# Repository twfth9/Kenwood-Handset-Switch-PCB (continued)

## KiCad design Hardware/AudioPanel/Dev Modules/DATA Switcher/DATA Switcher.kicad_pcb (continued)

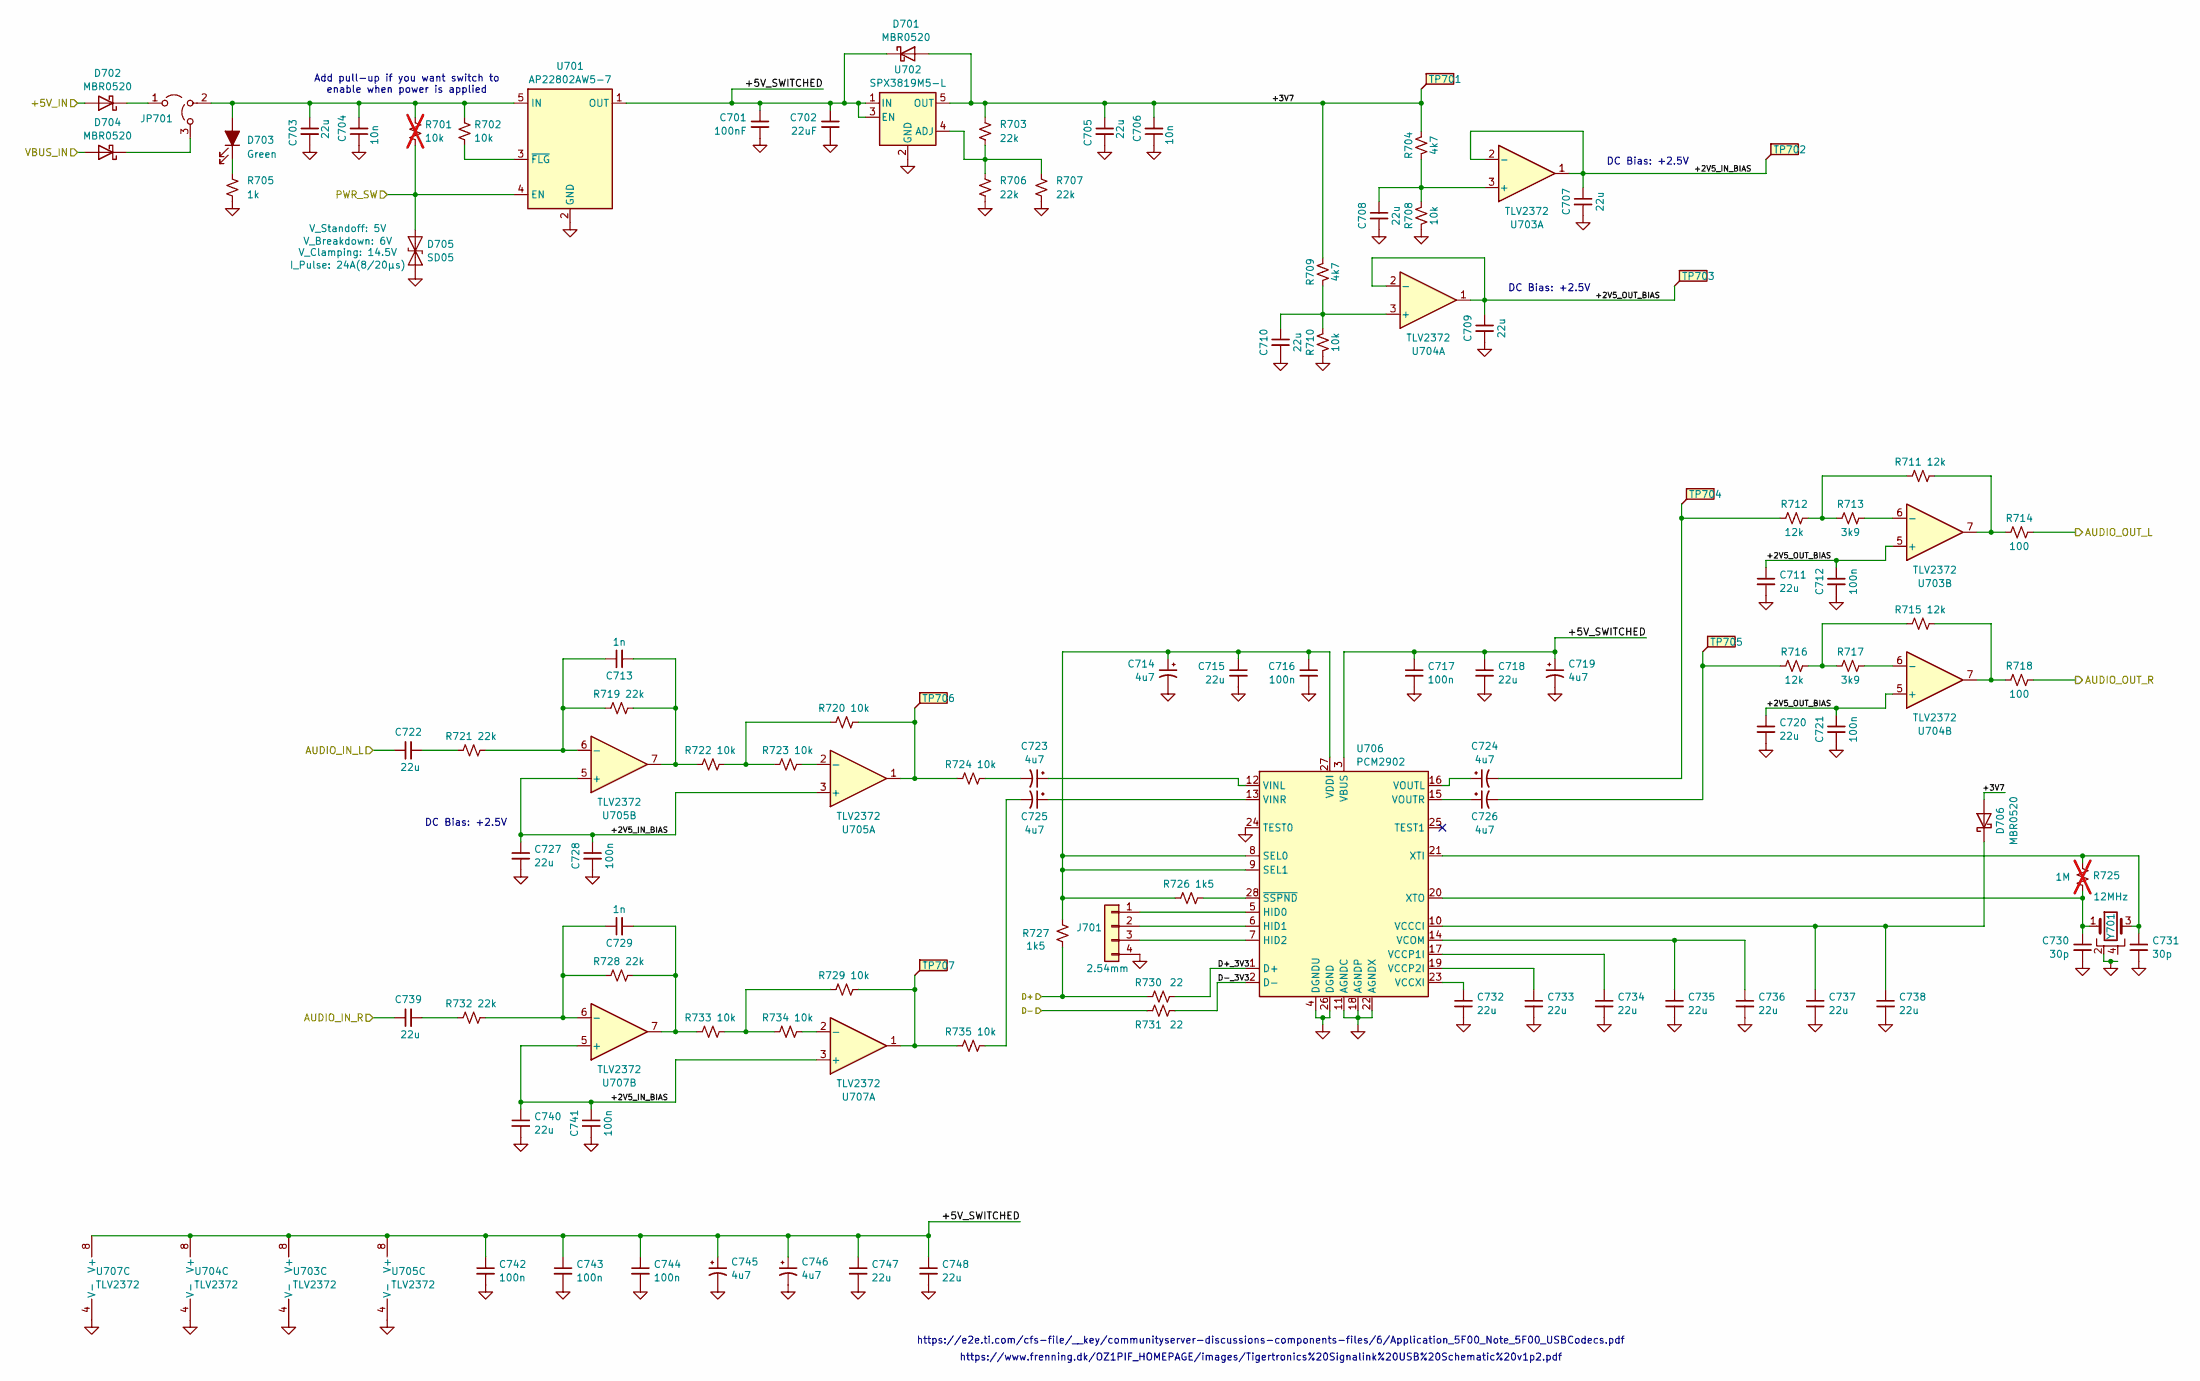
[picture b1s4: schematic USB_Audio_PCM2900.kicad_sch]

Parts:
C701: 100nF; Worthington_C_0402
C702: 22uF; Worthington_C_0603
C703, C705, C707, C708, C709, C710, C711, C715, C718, C720, C722, C727, C732, C733, C734, C735, C736, C737, C738, C739, C740, C747, C748: 22u; Worthington_C_0603
C704, C706: 10n; Worthington_C_0402
C712, C716, C717, C721, C728, C741, C742, C743, C744: 100n; Worthington_C_0402
C713, C729: 1n; Worthington_C_0402
C714, C719, C723, C724, C725, C726, C745, C746: 4u7; CP_EIA-3216-18_Kemet-A
C730, C731: 30p; Worthington_C_0402
D701, D702, D704, D706: MBR0520; D_SOD-123
D703: Green; Worthington_LED_0603; DigiKey Part Number 732-5016-ND
D705: SD05; D_SOD-323
J701: 2.54mm; PinHeader_1x04_P2.54mm_Vertical
JP701: Jumper_3_Open; SolderBridge_3L
R701: 10k; Worthington_R_0402; not fitted
R702, R708, R710, R720, R722, R723, R724, R729, R733, R734, R735: 10k; Worthington_R_0402
R703, R706, R707: 22k; Worthington_R_0402; DigiKey Part Number 311-510HRCT-ND
R704, R709: 4k7; Worthington_R_0402
R705: 1k; Worthington_R_0402; DigiKey Part Number 311-510HRCT-ND
R711, R712, R715, R716: 12k; Worthington_R_0402
R713, R717: 3k9; Worthington_R_0402
R714, R718: 100; Worthington_R_0402
R719, R721, R728, R732: 22k; Worthington_R_0402
R725: 1M; Worthington_R_0402; not fitted
R726, R727: 1k5; Worthington_R_0402
R730, R731: 22; Worthington_R_0402
TP701, TP702, TP703, TP704, TP705, TP706, TP707: TestPoint_Flag; KEYSTONE_5017
U701: AP22802AW5-7; SC-74A-5_1.55x2.9mm_P0.95mm
U702: SPX3819M5-L; SOT-23-5
U703, U704, U705, U707: TLV2372; SOIC-8_3.9x4.9mm_P1.27mm
U706: PCM2902; SSOP-28_5.3x10.2mm_P0.65mm
Y701: 12MHz; Crystal_SMD_Abracon_ABM8AIG-4Pin_3.2x2.5mm

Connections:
/+5V_RIGCTRL1: D702.2 (A); also elsewhere on the board
/RIGCTRL_1.D+: R727.2, R730.2; also elsewhere on the board
/RIGCTRL_1.D-: R731.1; also elsewhere on the board
/RIGCTRL_1.PWR_SW: D705.2 (A2), R701.2, U701.4 (EN); also elsewhere on the board
/RIGCTRL_1.RX1: C722.1; also elsewhere on the board
/RIGCTRL_1.RX2: C739.1; also elsewhere on the board
/RIGCTRL_1.TX1: R714.1; also elsewhere on the board
/RIGCTRL_1.TX2: R718.1; also elsewhere on the board
/RIGCTRL_1.VBUS: D704.2 (A); also elsewhere on the board
/USB Audio Interface - RIGCTRL1/+2V5_IN_BIAS: C707.1, C727.1, C728.1, C740.1, C741.1, TP702.1, U703.1, U703.2 (-), U705.3 (+), U705.5 (+), U707.3 (+), U707.5 (+)
/USB Audio Interface - RIGCTRL1/+2V5_OUT_BIAS: C709.1, C711.1, C712.1, C720.1, C721.1, TP703.1, U703.5 (+), U704.1, U704.2 (-), U704.5 (+)
/USB Audio Interface - RIGCTRL1/+3V7: C705.1, C706.2, D701.2 (A), D706.2 (A), R703.2, R704.2, R709.2, TP701.1, U702.5 (OUT)
/USB Audio Interface - RIGCTRL1/+5V_SWITCHED: C701.1, C702.1, C717.1, C718.1, C719.1, C742.1, C743.1, C744.1, C745.1, C746.1, C747.1, C748.1, D701.1 (K), U701.1 (OUT), U702.1 (IN), U702.3 (EN), U703.8 (V+), U704.8 (V+), U705.8 (V+), U706.3 (VBUS), U707.8 (V+)
/USB Audio Interface - RIGCTRL1/D+_3V3: R730.1, U706.1 (D+)
/USB Audio Interface - RIGCTRL1/D-_3V3: R731.2, U706.2 (D-)
GND: C701.2, C702.2, C703.2, C704.1, C705.2, C706.1, C707.2, C708.2, C709.2, C710.2, C711.2, C712.2, C714.2, C715.2, C716.2, C717.2, C718.2, C719.2, C720.2, C721.2, C727.2, C728.2, C730.2, C731.2, C732.2, C733.2, C734.2, C735.2, C736.2, C737.2, C738.2, C740.2, C741.2, C742.2, C743.2, C744.2, C745.2, C746.2, C747.2, C748.2, D705.1 (A1), J701.4, R705.1, R706.1, R707.1, R708.1, R710.1, U701.2 (GND), U702.2 (GND), U703.4 (V-), U704.4 (V-), U705.4 (V-), U706.4 (DGNDU), U706.11 (AGNDC), U706.18 (AGNDP), U706.22 (AGNDX), U706.24 (TEST0), U706.26 (DGND), U707.4 (V-), Y701.2; also elsewhere on the board
unnamed: C713.2, R719.1, R722.2, U705.7
unnamed: C722.2, R721.2
unnamed: C723.2, R724.1
unnamed: C724.2, R712.2, TP704.1
unnamed: C725.2, R735.1
unnamed: C726.2, R716.2, TP705.1
unnamed: C729.2, R728.1, R733.2, U707.7
unnamed: C739.2, R732.2
unnamed: D702.1 (K), JP701.1 (A)
unnamed: C703.1, C704.2, D703.2 (A), JP701.2 (C), R701.1, R702.1, U701.5 (IN)
unnamed: D703.1 (K), R705.2
unnamed: D704.1 (K), JP701.3 (B)
unnamed: C737.1, C738.1, D706.1 (K), U706.10 (VCCCI)
unnamed: J701.1, U706.5 (HID0)
unnamed: J701.2, U706.6 (HID1)
unnamed: J701.3, U706.7 (HID2)
unnamed: R711.1, R714.2, U703.7
unnamed: R711.2, R712.1, R713.2
unnamed: R715.1, R718.2, U704.7
unnamed: R715.2, R716.1, R717.2
unnamed: R720.1, R724.2, TP706.1, U705.1
unnamed: R720.2, R722.1, R723.2
unnamed: R729.1, R735.2, TP707.1, U707.1
unnamed: R729.2, R733.1, R734.2
unnamed: R702.2, U701.3 (~FLG)
unnamed: R703.1, R706.2, R707.2, U702.4 (ADJ)
unnamed: C708.1, R704.1, R708.2, U703.3 (+)
unnamed: R713.1, U703.6 (-)
unnamed: C710.1, R709.1, R710.2, U704.3 (+)
unnamed: R717.1, U704.6 (-)
unnamed: R723.1, U705.2 (-)
unnamed: C713.1, R719.2, R721.1, U705.6 (-)
unnamed: C714.1, C715.1, C716.1, R726.2, R727.1, U706.8 (SEL0), U706.9 (SEL1), U706.27 (VDDI)
unnamed: C734.1, U706.17 (VCCP1I)
unnamed: C733.1, U706.19 (VCCP2I)
unnamed: C732.1, U706.23 (VCCXI)
unnamed: C735.1, C736.1, U706.14 (VCOM)
unnamed: C723.1, U706.12 (VINL)
unnamed: C725.1, U706.13 (VINR)
unnamed: C724.1, U706.16 (VOUTL)
unnamed: C726.1, U706.15 (VOUTR)
unnamed: C731.1, R725.1, U706.21 (XTI), Y701.3
unnamed: C730.1, R725.2, U706.20 (XTO), Y701.1
unnamed: R726.1, U706.28 (~SSPND)
unnamed: R734.1, U707.2 (-)
unnamed: C729.1, R728.2, R732.1, U707.6 (-)

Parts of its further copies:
C801: 100nF; Worthington_C_0402
C802: 22uF; Worthington_C_0603
C803, C805, C807, C808, C809, C810, C811, C815, C818, C820, C822, C827, C832, C833, C834, C835, C836, C837, C838, C839, C840, C847, C848: 22u; Worthington_C_0603
C804, C806: 10n; Worthington_C_0402
C812, C816, C817, C821, C828, C841, C842, C843, C844: 100n; Worthington_C_0402
C813, C829: 1n; Worthington_C_0402
C814, C819, C823, C824, C825, C826, C845, C846: 4u7; CP_EIA-3216-18_Kemet-A
C830, C831: 30p; Worthington_C_0402
D801, D802, D804, D806: MBR0520; D_SOD-123
D803: Green; Worthington_LED_0603; DigiKey Part Number 732-5016-ND
D805: SD05; D_SOD-323
J801: 2.54mm; PinHeader_1x04_P2.54mm_Vertical
JP801: Jumper_3_Open; SolderBridge_3L
R801: 10k; Worthington_R_0402; not fitted
R802, R808, R810, R820, R822, R823, R824, R829, R833, R834, R835: 10k; Worthington_R_0402
R803, R806, R807: 22k; Worthington_R_0402; DigiKey Part Number 311-510HRCT-ND
R804, R809: 4k7; Worthington_R_0402
R805: 1k; Worthington_R_0402; DigiKey Part Number 311-510HRCT-ND
R811, R812, R815, R816: 12k; Worthington_R_0402
R813, R817: 3k9; Worthington_R_0402
R814, R818: 100; Worthington_R_0402
R819, R821, R828, R832: 22k; Worthington_R_0402
R825: 1M; Worthington_R_0402; not fitted
R826, R827: 1k5; Worthington_R_0402
R830, R831: 22; Worthington_R_0402
TP801, TP802, TP803, TP804, TP805, TP806, TP807: TestPoint_Flag; KEYSTONE_5017
U801: AP22802AW5-7; SC-74A-5_1.55x2.9mm_P0.95mm
U802: SPX3819M5-L; SOT-23-5
U803, U804, U805, U807: TLV2372; SOIC-8_3.9x4.9mm_P1.27mm
U806: PCM2902; SSOP-28_5.3x10.2mm_P0.65mm
Y801: 12MHz; Crystal_SMD_Abracon_ABM8AIG-4Pin_3.2x2.5mm

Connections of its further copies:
/+5V_RIGCTRL2: D802.2 (A); also elsewhere on the board
/RIGCTRL_2.D+: R827.2, R830.2; also elsewhere on the board
/RIGCTRL_2.D-: R831.1; also elsewhere on the board
/RIGCTRL_2.PWR_SW: D805.2 (A2), R801.2, U801.4 (EN); also elsewhere on the board
/RIGCTRL_2.RX1: C822.1; also elsewhere on the board
/RIGCTRL_2.RX2: C839.1; also elsewhere on the board
/RIGCTRL_2.TX1: R814.1; also elsewhere on the board
/RIGCTRL_2.TX2: R818.1; also elsewhere on the board
/RIGCTRL_2.VBUS: D804.2 (A); also elsewhere on the board
/USB Audio Interface - RIGCTRL2/+2V5_IN_BIAS: C807.1, C827.1, C828.1, C840.1, C841.1, TP802.1, U803.1, U803.2 (-), U805.3 (+), U805.5 (+), U807.3 (+), U807.5 (+)
/USB Audio Interface - RIGCTRL2/+2V5_OUT_BIAS: C809.1, C811.1, C812.1, C820.1, C821.1, TP803.1, U803.5 (+), U804.1, U804.2 (-), U804.5 (+)
/USB Audio Interface - RIGCTRL2/+3V7: C805.1, C806.2, D801.2 (A), D806.2 (A), R803.2, R804.2, R809.2, TP801.1, U802.5 (OUT)
/USB Audio Interface - RIGCTRL2/+5V_SWITCHED: C801.1, C802.1, C817.1, C818.1, C819.1, C842.1, C843.1, C844.1, C845.1, C846.1, C847.1, C848.1, D801.1 (K), U801.1 (OUT), U802.1 (IN), U802.3 (EN), U803.8 (V+), U804.8 (V+), U805.8 (V+), U806.3 (VBUS), U807.8 (V+)
/USB Audio Interface - RIGCTRL2/D+_3V3: R830.1, U806.1 (D+)
/USB Audio Interface - RIGCTRL2/D-_3V3: R831.2, U806.2 (D-)
GND: C801.2, C802.2, C803.2, C804.1, C805.2, C806.1, C807.2, C808.2, C809.2, C810.2, C811.2, C812.2, C814.2, C815.2, C816.2, C817.2, C818.2, C819.2, C820.2, C821.2, C827.2, C828.2, C830.2, C831.2, C832.2, C833.2, C834.2, C835.2, C836.2, C837.2, C838.2, C840.2, C841.2, C842.2, C843.2, C844.2, C845.2, C846.2, C847.2, C848.2, D805.1 (A1), J801.4, R805.1, R806.1, R807.1, R808.1, R810.1, U801.2 (GND), U802.2 (GND), U803.4 (V-), U804.4 (V-), U805.4 (V-), U806.4 (DGNDU), U806.11 (AGNDC), U806.18 (AGNDP), U806.22 (AGNDX), U806.24 (TEST0), U806.26 (DGND), U807.4 (V-), Y801.2; also elsewhere on the board
unnamed: C813.2, R819.1, R822.2, U805.7
unnamed: C822.2, R821.2
unnamed: C823.2, R824.1
unnamed: C824.2, R812.2, TP804.1
unnamed: C825.2, R835.1
unnamed: C826.2, R816.2, TP805.1
unnamed: C829.2, R828.1, R833.2, U807.7
unnamed: C839.2, R832.2
unnamed: D802.1 (K), JP801.1 (A)
unnamed: C803.1, C804.2, D803.2 (A), JP801.2 (C), R801.1, R802.1, U801.5 (IN)
unnamed: D803.1 (K), R805.2
unnamed: D804.1 (K), JP801.3 (B)
unnamed: C837.1, C838.1, D806.1 (K), U806.10 (VCCCI)
unnamed: J801.1, U806.5 (HID0)
unnamed: J801.2, U806.6 (HID1)
unnamed: J801.3, U806.7 (HID2)
unnamed: R811.1, R814.2, U803.7
unnamed: R811.2, R812.1, R813.2
unnamed: R815.1, R818.2, U804.7
unnamed: R815.2, R816.1, R817.2
unnamed: R820.1, R824.2, TP806.1, U805.1
unnamed: R820.2, R822.1, R823.2
unnamed: R829.1, R835.2, TP807.1, U807.1
unnamed: R829.2, R833.1, R834.2
unnamed: R802.2, U801.3 (~FLG)
unnamed: R803.1, R806.2, R807.2, U802.4 (ADJ)
unnamed: C808.1, R804.1, R808.2, U803.3 (+)
unnamed: R813.1, U803.6 (-)
unnamed: C810.1, R809.1, R810.2, U804.3 (+)
unnamed: R817.1, U804.6 (-)
unnamed: R823.1, U805.2 (-)
unnamed: C813.1, R819.2, R821.1, U805.6 (-)
unnamed: C814.1, C815.1, C816.1, R826.2, R827.1, U806.8 (SEL0), U806.9 (SEL1), U806.27 (VDDI)
unnamed: C834.1, U806.17 (VCCP1I)
unnamed: C833.1, U806.19 (VCCP2I)
unnamed: C832.1, U806.23 (VCCXI)
unnamed: C835.1, C836.1, U806.14 (VCOM)
unnamed: C823.1, U806.12 (VINL)
unnamed: C825.1, U806.13 (VINR)
unnamed: C824.1, U806.16 (VOUTL)
unnamed: C826.1, U806.15 (VOUTR)
unnamed: C831.1, R825.1, U806.21 (XTI), Y801.3
unnamed: C830.1, R825.2, U806.20 (XTO), Y801.1
unnamed: R826.1, U806.28 (~SSPND)
unnamed: R834.1, U807.2 (-)
unnamed: C829.1, R828.2, R832.1, U807.6 (-)

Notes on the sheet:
DC Bias: +2.5V
Add pull-up if you want switch to enable when power is applied
https://www.frenning.dk/OZ1PIF_HOMEPAGE/images/Tigertronics%20Signalink%20USB%20Schematic%20v1p2.pdf
https://e2e.ti.com/cfs-file/__key/communityserver-discussions-components-files/6/Application_5F00_Note_5F00_USBCodecs.pdf

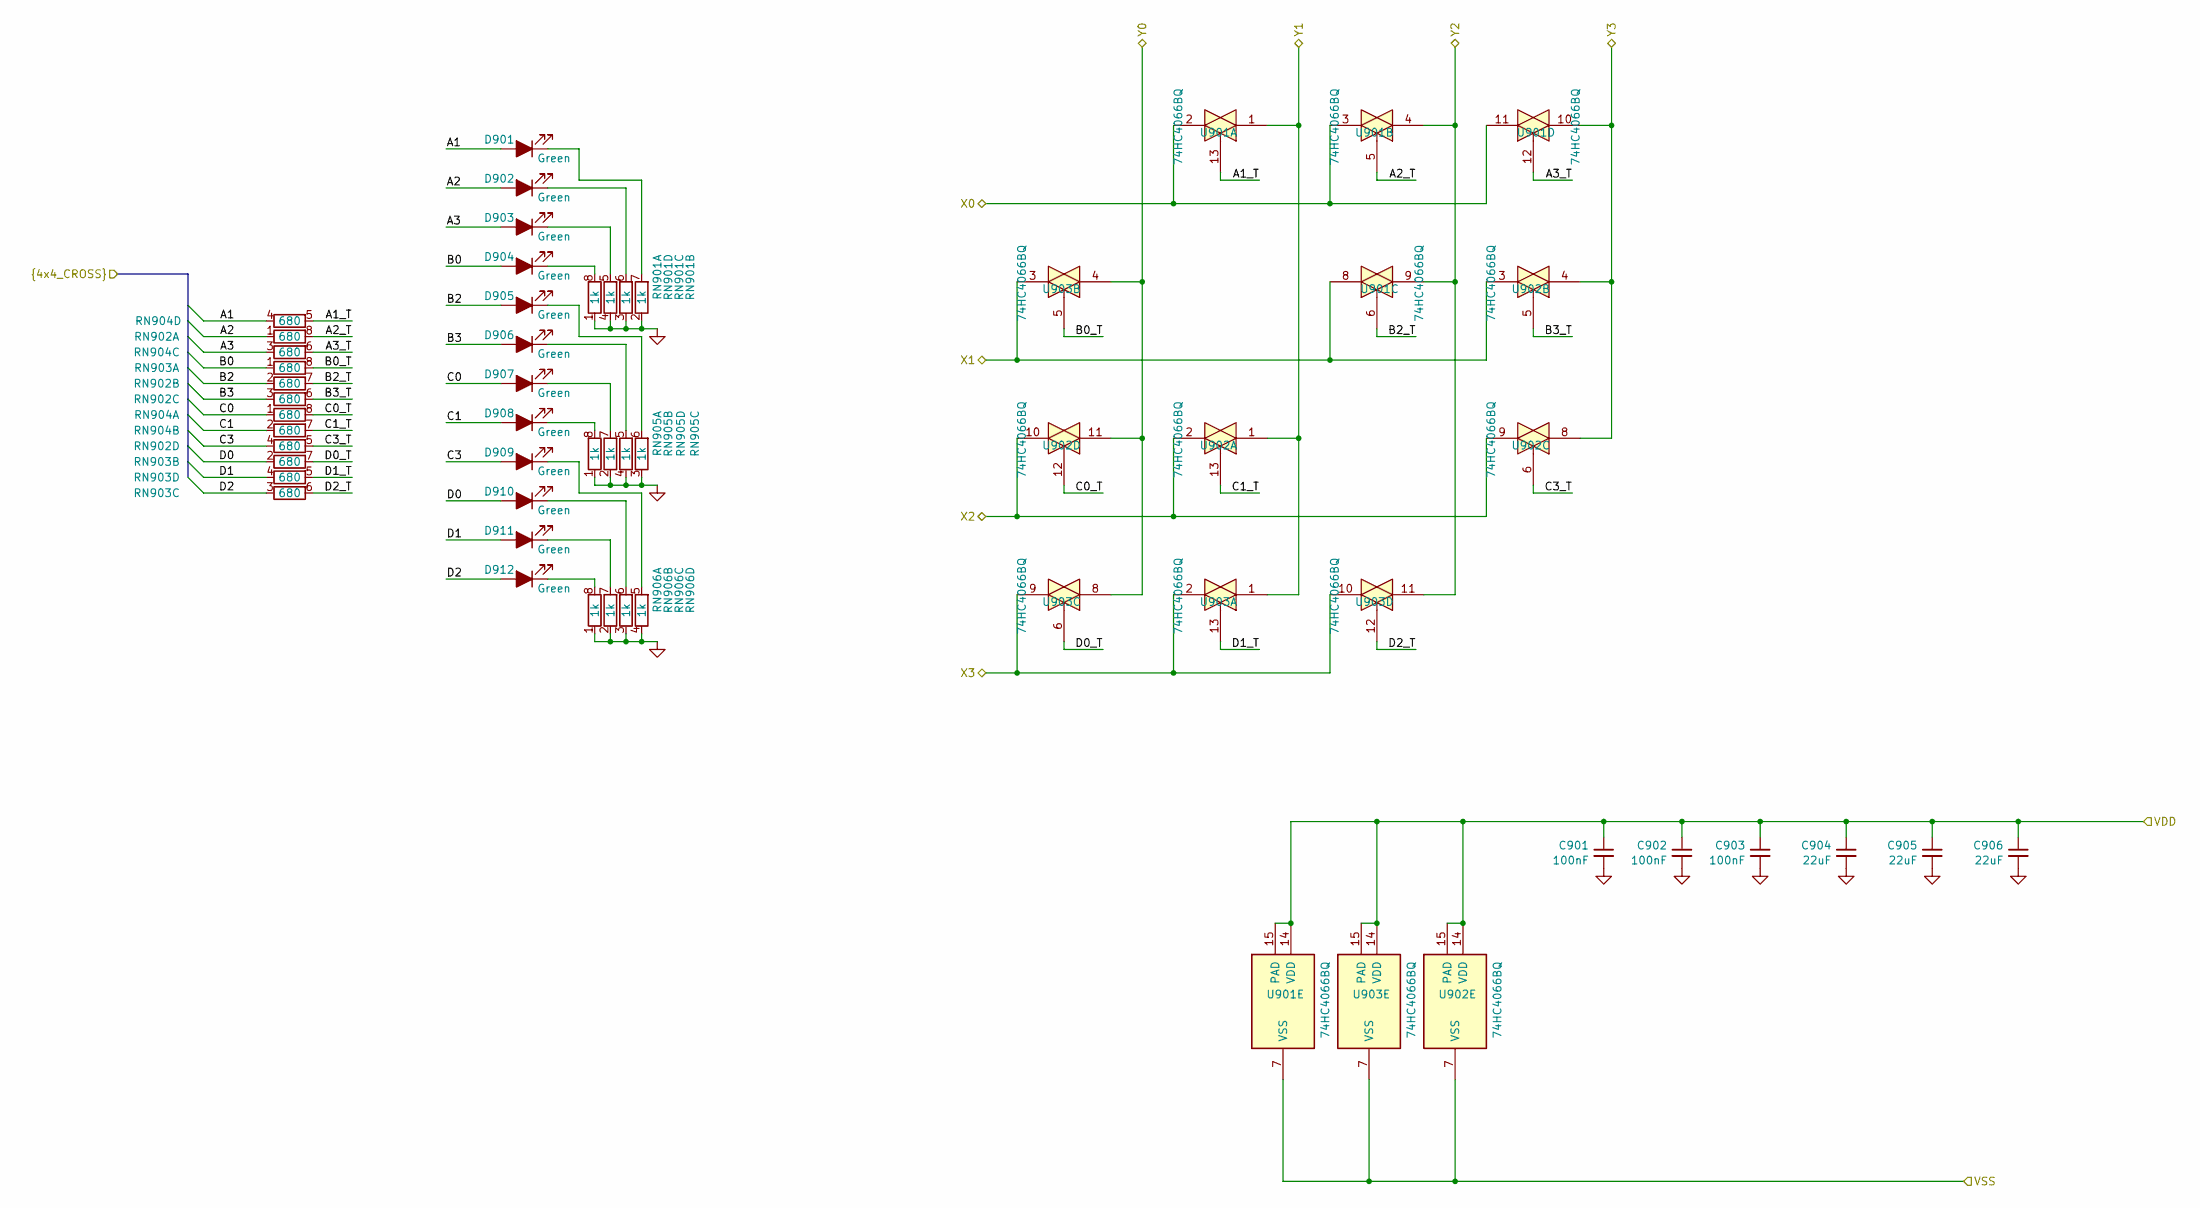
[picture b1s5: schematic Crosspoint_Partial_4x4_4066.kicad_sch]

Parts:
C901, C902, C903: 100nF; Worthington_C_0402
C904, C905, C906: 22uF; Worthington_C_0603
D901, D902, D903, D904, D905, D906, D907, D908, D909, D910, D911, D912: Green; Worthington_LED_0603; DigiKey Part Number 732-5016-ND
RN901, RN905, RN906: 1k; RES_ARRAY_4RES_0804
RN902, RN903, RN904: 680; RES_ARRAY_4RES_0804
U901, U902, U903: 74HC4066BQ; QFN_104BQX_NEX

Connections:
/4x4 Analog Crosspoint Switch/A1: D901.2 (A), RN904.4; also elsewhere on the board
/4x4 Analog Crosspoint Switch/A1_T: RN904.5, U901.13
/4x4 Analog Crosspoint Switch/A2: D902.2 (A), RN902.1 (4); also elsewhere on the board
/4x4 Analog Crosspoint Switch/A2_T: RN902.8, U901.5
/4x4 Analog Crosspoint Switch/A3: D903.2 (A), RN904.3; also elsewhere on the board
/4x4 Analog Crosspoint Switch/A3_T: RN904.6, U901.12
/4x4 Analog Crosspoint Switch/B0: D904.2 (A), RN903.1 (4); also elsewhere on the board
/4x4 Analog Crosspoint Switch/B0_T: RN903.8, U903.5
/4x4 Analog Crosspoint Switch/B2: D905.2 (A), RN902.2; also elsewhere on the board
/4x4 Analog Crosspoint Switch/B2_T: RN902.7 (5), U901.6
/4x4 Analog Crosspoint Switch/B3: D906.2 (A), RN902.3; also elsewhere on the board
/4x4 Analog Crosspoint Switch/B3_T: RN902.6, U902.5
/4x4 Analog Crosspoint Switch/C0: D907.2 (A), RN904.1 (4); also elsewhere on the board
/4x4 Analog Crosspoint Switch/C0_T: RN904.8, U902.12
/4x4 Analog Crosspoint Switch/C1: D908.2 (A), RN904.2; also elsewhere on the board
/4x4 Analog Crosspoint Switch/C1_T: RN904.7 (5), U902.13
/4x4 Analog Crosspoint Switch/C3: D909.2 (A), RN902.4; also elsewhere on the board
/4x4 Analog Crosspoint Switch/C3_T: RN902.5, U902.6
/4x4 Analog Crosspoint Switch/D0: D910.2 (A), RN903.2; also elsewhere on the board
/4x4 Analog Crosspoint Switch/D0_T: RN903.7 (5), U903.6
/4x4 Analog Crosspoint Switch/D1: D911.2 (A), RN903.4; also elsewhere on the board
/4x4 Analog Crosspoint Switch/D1_T: RN903.5, U903.13
/4x4 Analog Crosspoint Switch/D2: D912.2 (A), RN903.3; also elsewhere on the board
/4x4 Analog Crosspoint Switch/D2_T: RN903.6, U903.12
/480_DATA.RX_MUX: U901.2, U901.3, U901.11; also elsewhere on the board
/480_DATA.TX_MUX: U902.11, U903.4, U903.8; also elsewhere on the board
/700_DATA.RX_MUX: U902.2, U902.9, U902.10; also elsewhere on the board
/700_DATA.TX_MUX: U901.4, U901.9, U903.11; also elsewhere on the board
/710_DATA.RX_MUX: U901.8, U902.3, U903.3; also elsewhere on the board
/710_DATA.TX_MUX: U901.1, U902.1, U903.1; also elsewhere on the board
/+5V_CROSSPOINT: C901.1, C902.1, C903.1, C904.1, C905.1, C906.1, U901.14 (VDD), U901.15 (PAD), U902.14 (VDD), U902.15 (PAD), U903.14 (VDD), U903.15 (PAD); also elsewhere on the board
/EXTRA_DATA.RX_MUX: U903.2, U903.9, U903.10; also elsewhere on the board
/EXTRA_DATA.TX_MUX: U901.10, U902.4, U902.8; also elsewhere on the board
GND: C901.2, C902.2, C903.2, C904.2, C905.2, C906.2, RN901.1 (4), RN901.2, RN901.3, RN901.4, RN905.1 (4), RN905.2, RN905.3, RN905.4, RN906.1 (4), RN906.2, RN906.3, RN906.4, U901.7 (VSS), U902.7 (VSS), U903.7 (VSS); also elsewhere on the board
unnamed: D901.1 (K), RN901.7 (5)
unnamed: D902.1 (K), RN901.6
unnamed: D903.1 (K), RN901.5
unnamed: D904.1 (K), RN901.8
unnamed: D905.1 (K), RN905.6
unnamed: D906.1 (K), RN905.5
unnamed: D907.1 (K), RN905.7 (5)
unnamed: D908.1 (K), RN905.8
unnamed: D909.1 (K), RN906.5
unnamed: D910.1 (K), RN906.6
unnamed: D911.1 (K), RN906.7 (5)
unnamed: D912.1 (K), RN906.8

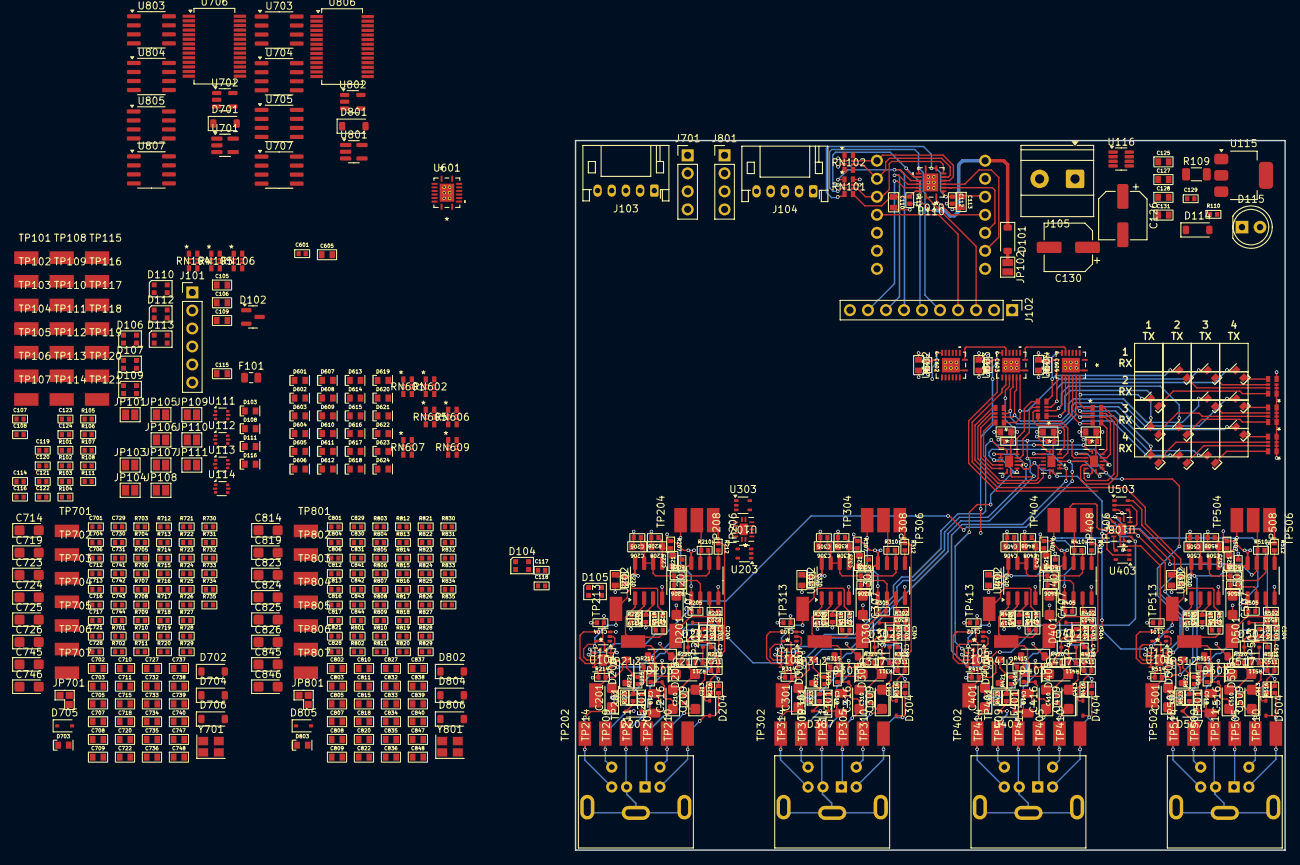
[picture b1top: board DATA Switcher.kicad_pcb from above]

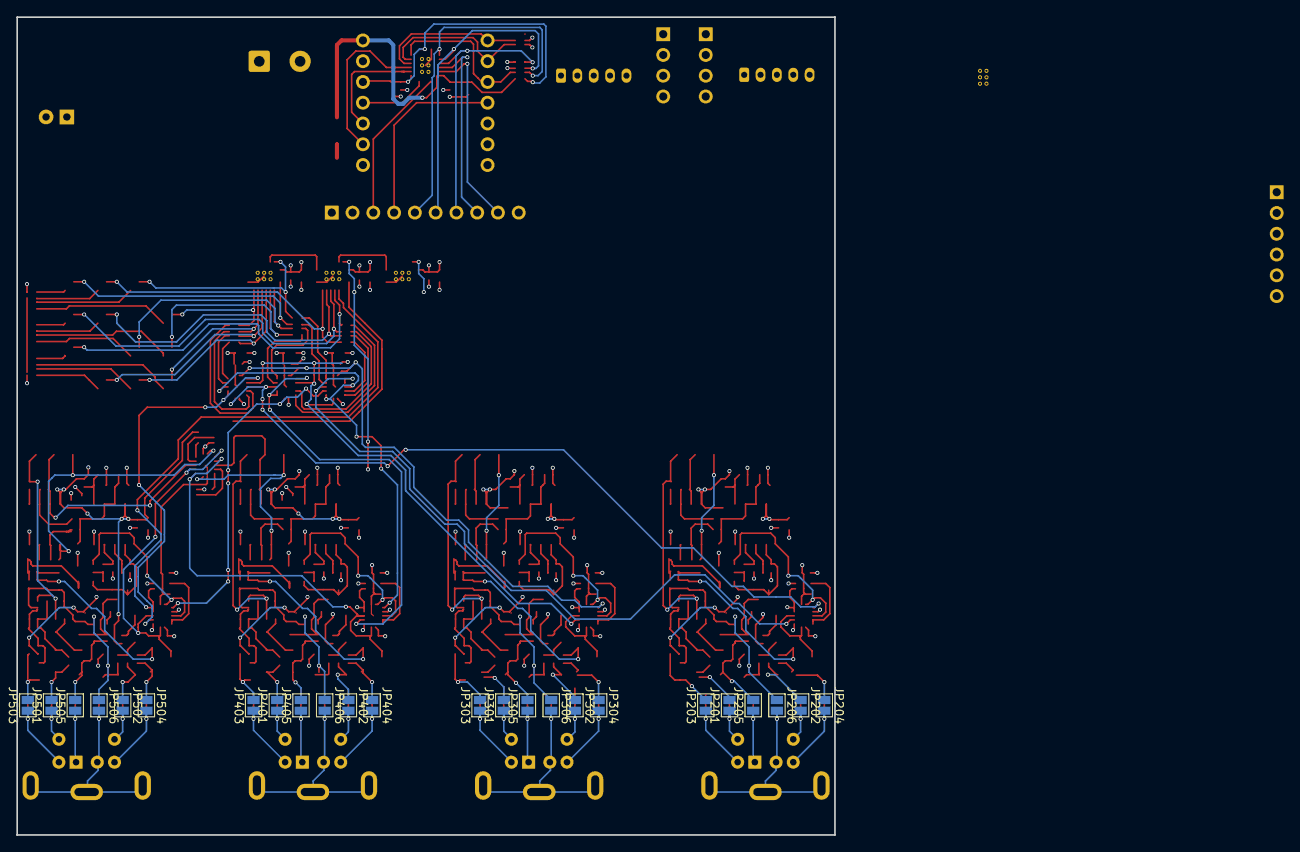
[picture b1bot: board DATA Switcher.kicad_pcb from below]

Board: 4 copper layers, 100.0 x 100.0 mm, 704 parts (24 on the bottom side), 399 nets.
